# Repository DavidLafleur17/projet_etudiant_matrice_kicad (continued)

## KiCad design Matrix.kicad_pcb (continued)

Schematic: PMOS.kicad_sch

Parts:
Q2, Q3, Q4, Q5, Q6, Q7, Q8, Q9, Q10, Q11, Q12, Q13, Q14, Q15, Q16, Q17: PMOS; GSF3407; DigiKey PN 4786-GSFC3401CT-ND

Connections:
+5V: Q2.3 (S), Q3.3 (S), Q4.3 (S), Q5.3 (S), Q6.3 (S), Q7.3 (S), Q8.3 (S), Q9.3 (S), Q10.3 (S), Q11.3 (S), Q12.3 (S), Q13.3 (S), Q14.3 (S), Q15.3 (S), Q16.3 (S), Q17.3 (S); also elsewhere on the board
/Decoder/PMOS/DEC0: Q2.2 (G); also elsewhere on the board
/Decoder/PMOS/DEC1: Q3.2 (G); also elsewhere on the board
/Decoder/PMOS/DEC2: Q4.2 (G); also elsewhere on the board
/Decoder/PMOS/DEC3: Q5.2 (G); also elsewhere on the board
/Decoder/PMOS/DEC4: Q6.2 (G); also elsewhere on the board
/Decoder/PMOS/DEC5: Q7.2 (G); also elsewhere on the board
/Decoder/PMOS/DEC6: Q8.2 (G); also elsewhere on the board
/Decoder/PMOS/DEC7: Q9.2 (G); also elsewhere on the board
/Decoder/PMOS/DEC8: Q10.2 (G); also elsewhere on the board
/Decoder/PMOS/DEC9: Q11.2 (G); also elsewhere on the board
/Decoder/PMOS/DEC10: Q12.2 (G); also elsewhere on the board
/Decoder/PMOS/DEC11: Q13.2 (G); also elsewhere on the board
/Decoder/PMOS/DEC12: Q14.2 (G); also elsewhere on the board
/Decoder/PMOS/DEC13: Q15.2 (G); also elsewhere on the board
/Decoder/PMOS/DEC14: Q16.2 (G); also elsewhere on the board
/Decoder/PMOS/DEC15: Q17.2 (G); also elsewhere on the board
/Decoder/Row0: Q2.1 (D); also elsewhere on the board
/Decoder/Row1: Q3.1 (D); also elsewhere on the board
/Decoder/Row2: Q4.1 (D); also elsewhere on the board
/Decoder/Row3: Q5.1 (D); also elsewhere on the board
/Decoder/Row4: Q6.1 (D); also elsewhere on the board
/Decoder/Row5: Q7.1 (D); also elsewhere on the board
/Decoder/Row6: Q8.1 (D); also elsewhere on the board
/Decoder/Row7: Q9.1 (D); also elsewhere on the board
/Decoder/Row8: Q10.1 (D); also elsewhere on the board
/Decoder/Row9: Q11.1 (D); also elsewhere on the board
/Decoder/Row10: Q12.1 (D); also elsewhere on the board
/Decoder/Row11: Q13.1 (D); also elsewhere on the board
/Decoder/Row12: Q14.1 (D); also elsewhere on the board
/Decoder/Row13: Q15.1 (D); also elsewhere on the board
/Decoder/Row14: Q16.1 (D); also elsewhere on the board
/Decoder/Row15: Q17.1 (D); also elsewhere on the board

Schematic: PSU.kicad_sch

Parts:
C17, C18: 100nF; C_0805_2012Metric_Pad1.18x1.45mm_HandSolder; DigiKey PN 399-C0805F104K1RACAUTOCT-ND
C28: 47uF; CP_Elec_6.3x5.9; DigiKey PN EMZJ350ARA470MF61G
C29: 22nF; C_0805_2012Metric_Pad1.18x1.45mm_HandSolder; DigiKey PN 399-C0805C223K5RACTUCT-ND
D514: SMAJ5.0A; P6SMAJ5.0; DigiKey PN 31-P6SMAJ5.0ADF-13CT-ND
F1: 1.75A; Fuse_1206_3216Metric_Pad1.42x1.75mm_HandSolder; DigiKey PN 13-SMD1206B175TFCT-ND
J3: PSU HDR (mâle); PinHeader_1x03_P2.54mm_Horizontal; DigiKey PN S9403-ND
J5: PSU HDR (femelle); DigiKey PN S9434-ND
J9: Barrel_Jack_Switch; DigiKey PN CP-038A-ND
Q1: NMOS; GSF3407; DigiKey PN 4786-GSF3404BCT-ND
R32: 100kΩ; R_0805_2012Metric_Pad1.20x1.40mm_HandSolder; DigiKey PN 2019-RK73H2ATTD1003FCT-ND
U12: LM74700Q; TSOT-23-6_HandSoldering; DigiKey PN 296-LM74700QDBVRQ1CT-ND

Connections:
/Alimentation/PSU/PSU_V+: C18.1, C28.1, Q1.1 (D), U12.4 (CATHODE); also elsewhere on the board
GND: C18.2, C28.2, C29.2, D514.2 (A2), J3.2, J3.3, U12.2 (GND); also elsewhere on the board
unnamed: D514.1 (A1), F1.1, J3.1
unnamed: Q1.2 (G), U12.5 (GATE)
unnamed: C17.1, C29.1, F1.2, Q1.3 (S), R32.2, U12.6 (ANODE)
unnamed: R32.1, U12.3 (EN)
unnamed: C17.2, U12.1 (VCP)

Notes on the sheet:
Not on board

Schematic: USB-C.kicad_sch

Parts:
C1, C2: 100nF; C_0805_2012Metric_Pad1.18x1.45mm_HandSolder; DigiKey PN 399-C0805F104K1RACAUTOCT-ND
D513: SMAJ5.0A; P6SMAJ5.0; DigiKey PN 31-P6SMAJ5.0ADF-13CT-ND
D515, D516: ESD5V; D_0603_1608Metric_Pad1.05x0.95mm_HandSolder; DigiKey PN 31-D5V0S1U2LP1610-7CT-ND
J7: USB_C_Receptacle_USB2.0_16P; USB_C_Receptacle_GCT_USB4105-xx-A_16P_TopMnt_Horizontal; DigiKey PN 2223-UJ20-C-H-G-SMT-2A-P16-TRCT-ND
R1: 1MΩ; R_0805_2012Metric_Pad1.20x1.40mm_HandSolder; DigiKey PN 2019-RK73H2ATTD1004FCT-ND
R2, R3: 5.1kΩ; R_0805_2012Metric_Pad1.20x1.40mm_HandSolder; DigiKey PN 2019-RK73H2ATTD5101FCT-ND
R35: 33kΩ; R_0805_2012Metric_Pad1.20x1.40mm_HandSolder; DigiKey PN 2019-RK73H2ATTD3302FCT-ND
R36: 47kΩ; R_0805_2012Metric_Pad1.20x1.40mm_HandSolder; DigiKey PN 2019-RK73H2ATTD4702FCT-ND
R37: 1kΩ; R_0805_2012Metric_Pad1.20x1.40mm_HandSolder; DigiKey PN 2019-RK73H2ATTD1001FCT-ND

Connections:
/Alimentation/USB_D+: D515.2 (A2), J7.A6 (D+), J7.B6 (D+); also elsewhere on the board
/Alimentation/USB_D-: D516.2 (A2), J7.A7 (D-), J7.B7 (D-); also elsewhere on the board
/Alimentation/VBUS_SENSE: R37.1; also elsewhere on the board
GND: C1.2, C2.2, D513.2 (A2), D515.1 (A1), D516.1 (A1), J7.A1 (GND), J7.A12 (GND), J7.B1 (GND), J7.B12 (GND), R1.1, R2.1, R3.1, R36.2; also elsewhere on the board
unnamed: C2.1, R35.2, R36.1, R37.2
unnamed: D513.1 (A1), J7.A4 (VBUS), J7.A9 (VBUS), J7.B4 (VBUS), J7.B9 (VBUS), R35.1
unnamed: J7.A5 (CC1), R2.2
unnamed: J7.B5 (CC2), R3.2
unnamed: C1.1, J7.S1 (SHIELD), R1.2

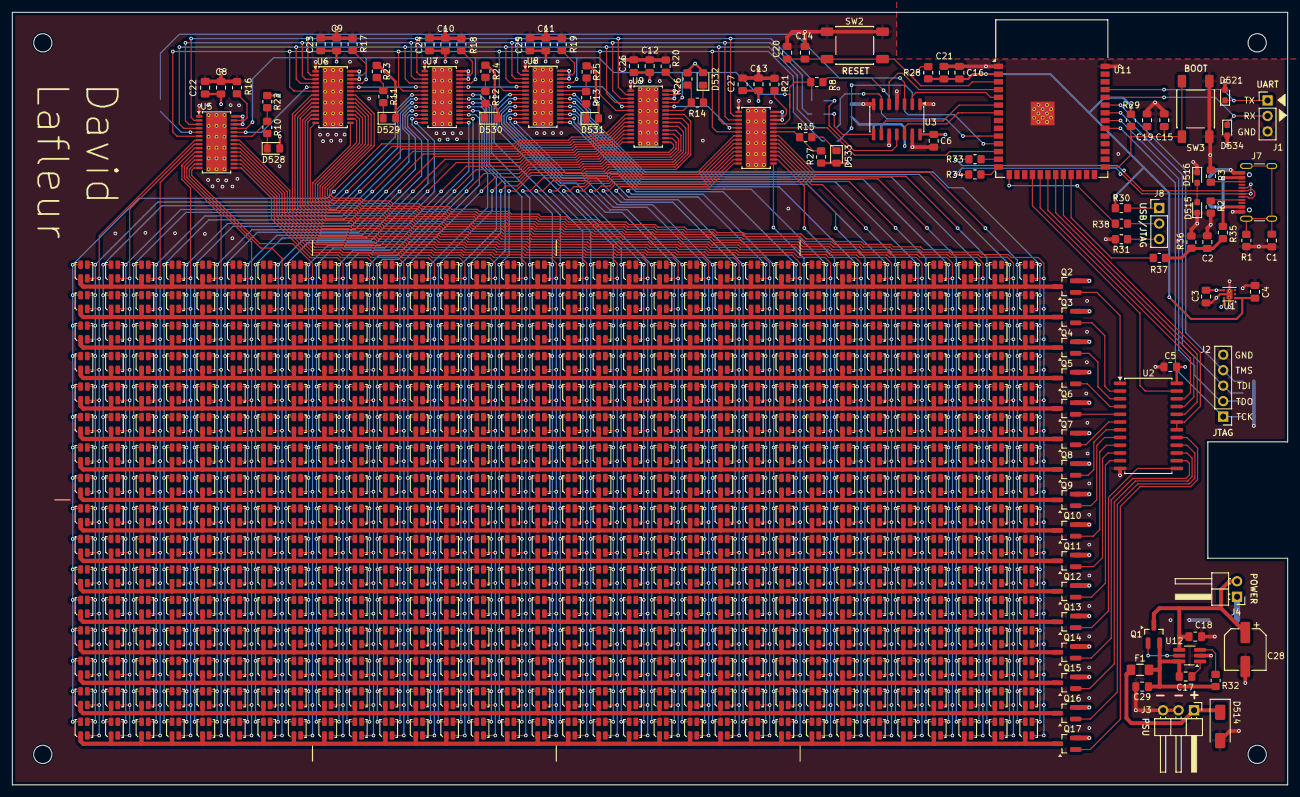
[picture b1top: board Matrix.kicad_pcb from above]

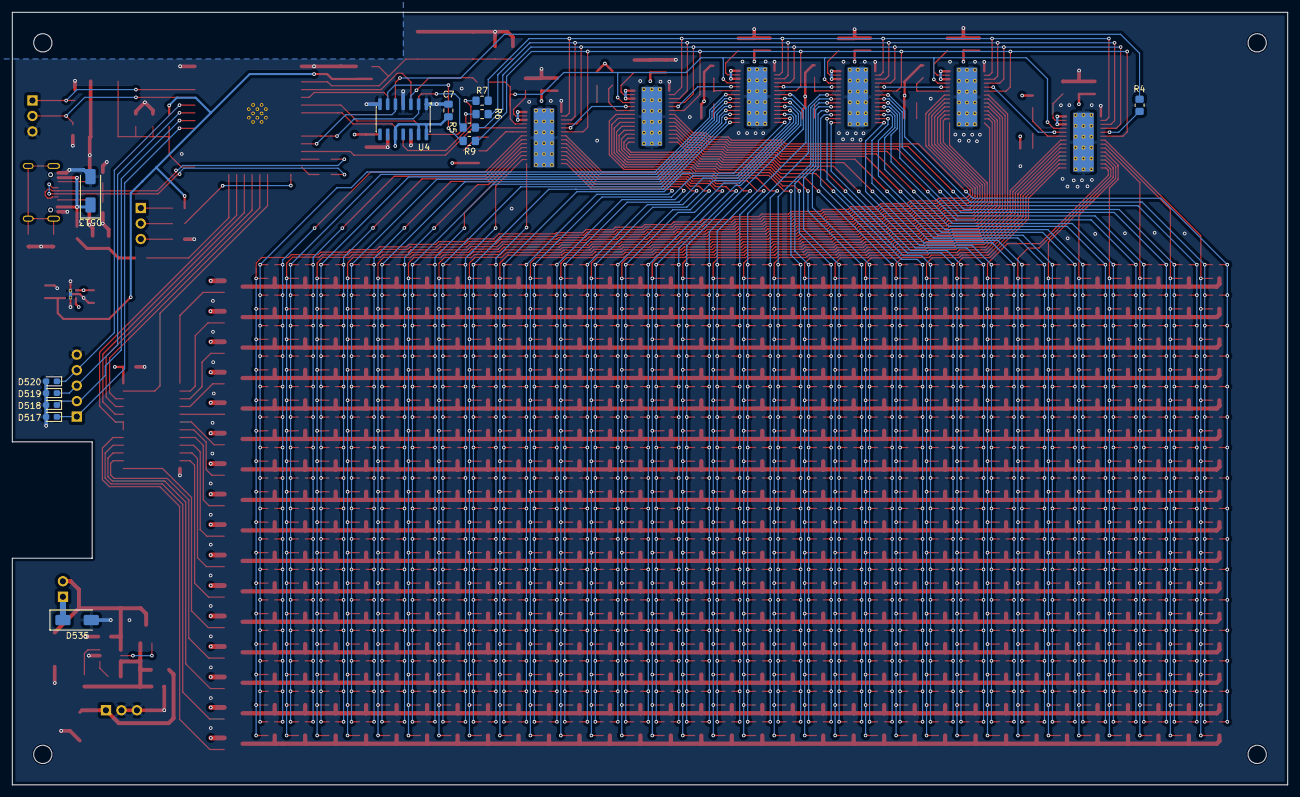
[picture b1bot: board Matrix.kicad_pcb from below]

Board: 4 copper layers, 209.2 x 126.8 mm, 638 parts (13 on the bottom side), 206 nets.

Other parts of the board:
U7, U8, U9, U10: TLC5940PWP; HTSSOP-28-1EP_4.4x9.7mm_P0.65mm_EP3.4x9.5mm_Mask2.4x6.17mm_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

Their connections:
+5V: U7.26 (DCPRG), U7.28 (VCC), U8.26 (DCPRG), U8.28 (VCC), U9.26 (DCPRG), U9.28 (VCC), U10.26 (DCPRG), U10.28 (VCC); also elsewhere on the board
/Blue0: U9.7 (OUT0); also elsewhere on the board
/Blue1: U9.8 (OUT1); also elsewhere on the board
/Blue2: U9.9 (OUT2); also elsewhere on the board
/Blue3: U9.10 (OUT3); also elsewhere on the board
/Blue4: U9.11 (OUT4); also elsewhere on the board
/Blue5: U9.12 (OUT5); also elsewhere on the board
/Blue6: U9.13 (OUT6); also elsewhere on the board
/Blue7: U9.14 (OUT7); also elsewhere on the board
/Blue8: U9.15 (OUT8); also elsewhere on the board
/Blue9: U9.16 (OUT9); also elsewhere on the board
/Blue10: U9.17 (OUT10); also elsewhere on the board
/Blue11: U9.18 (OUT11); also elsewhere on the board
/Blue12: U9.19 (OUT12); also elsewhere on the board
/Blue13: U9.20 (OUT13); also elsewhere on the board
/Blue14: U9.21 (OUT14); also elsewhere on the board
/Blue15: U9.22 (OUT15); also elsewhere on the board
/Blue16: U10.7 (OUT0); also elsewhere on the board
/Blue17: U10.8 (OUT1); also elsewhere on the board
/Blue18: U10.9 (OUT2); also elsewhere on the board
/Blue19: U10.10 (OUT3); also elsewhere on the board
/Blue20: U10.11 (OUT4); also elsewhere on the board
/Blue21: U10.12 (OUT5); also elsewhere on the board
/Blue22: U10.13 (OUT6); also elsewhere on the board
/Blue23: U10.14 (OUT7); also elsewhere on the board
/Blue24: U10.15 (OUT8); also elsewhere on the board
/Blue25: U10.16 (OUT9); also elsewhere on the board
/Blue26: U10.17 (OUT10); also elsewhere on the board
/Blue27: U10.18 (OUT11); also elsewhere on the board
/Blue28: U10.19 (OUT12); also elsewhere on the board
/Blue29: U10.20 (OUT13); also elsewhere on the board
/Blue30: U10.21 (OUT14); also elsewhere on the board
/Blue31: U10.22 (OUT15); also elsewhere on the board
/Green0: U7.7 (OUT0); also elsewhere on the board
/Green1: U7.8 (OUT1); also elsewhere on the board
/Green2: U7.9 (OUT2); also elsewhere on the board
/Green3: U7.10 (OUT3); also elsewhere on the board
/Green4: U7.11 (OUT4); also elsewhere on the board
/Green5: U7.12 (OUT5); also elsewhere on the board
/Green6: U7.13 (OUT6); also elsewhere on the board
/Green7: U7.14 (OUT7); also elsewhere on the board
/Green8: U7.15 (OUT8); also elsewhere on the board
/Green9: U7.16 (OUT9); also elsewhere on the board
/Green10: U7.17 (OUT10); also elsewhere on the board
/Green11: U7.18 (OUT11); also elsewhere on the board
/Green12: U7.19 (OUT12); also elsewhere on the board
/Green13: U7.20 (OUT13); also elsewhere on the board
/Green14: U7.21 (OUT14); also elsewhere on the board
/Green15: U7.22 (OUT15); also elsewhere on the board
/Green16: U8.7 (OUT0); also elsewhere on the board
/Green17: U8.8 (OUT1); also elsewhere on the board
/Green18: U8.9 (OUT2); also elsewhere on the board
/Green19: U8.10 (OUT3); also elsewhere on the board
/Green20: U8.11 (OUT4); also elsewhere on the board
/Green21: U8.12 (OUT5); also elsewhere on the board
/Green22: U8.13 (OUT6); also elsewhere on the board
/Green23: U8.14 (OUT7); also elsewhere on the board
/Green24: U8.15 (OUT8); also elsewhere on the board
/Green25: U8.16 (OUT9); also elsewhere on the board
/Green26: U8.17 (OUT10); also elsewhere on the board
/Green27: U8.18 (OUT11); also elsewhere on the board
/Green28: U8.19 (OUT12); also elsewhere on the board
/Green29: U8.20 (OUT13); also elsewhere on the board
/Green30: U8.21 (OUT14); also elsewhere on the board
/Green31: U8.22 (OUT15); also elsewhere on the board
/TLC_BLANK: U7.2 (BLANK), U8.2 (BLANK), U9.2 (BLANK), U10.2 (BLANK); also elsewhere on the board
/TLC_BLUE/TLC SIN: U8.24 (SOUT), U9.5 (SIN)
/TLC_GREEN/TLC SIN: U7.5 (SIN); also elsewhere on the board
/TLC_GSCLK: U7.25 (GSCLK), U8.25 (GSCLK), U9.25 (GSCLK), U10.25 (GSCLK); also elsewhere on the board
/TLC_SCLK: U7.4 (SCLK), U8.4 (SCLK), U9.4 (SCLK), U10.4 (SCLK); also elsewhere on the board
/TLC_VPRG: U7.6 (VPRG), U8.6 (VPRG), U9.6 (VPRG), U10.6 (VPRG); also elsewhere on the board
/TLC_XLAT: U7.3 (XLAT), U8.3 (XLAT), U9.3 (XLAT), U10.3 (XLAT); also elsewhere on the board
GND: U7.1 (GND), U7.29 (PAD), U8.1 (GND), U8.29 (PAD), U9.1 (GND), U9.29 (PAD), U10.1 (GND), U10.29 (PAD); also elsewhere on the board
unnamed 188: U7.27 (IREF); also elsewhere on the board
unnamed: U7.24 (SOUT), U8.5 (SIN)
unnamed 190: U7.23 (XERR); also elsewhere on the board
unnamed 191: U8.27 (IREF); also elsewhere on the board
unnamed 192: U8.23 (XERR); also elsewhere on the board
unnamed 193: U9.27 (IREF); also elsewhere on the board
unnamed 194: U9.23 (XERR); also elsewhere on the board
unnamed 195: U10.27 (IREF); also elsewhere on the board
unnamed: U9.24 (SOUT), U10.5 (SIN)
unnamed 197: U10.23 (XERR); also elsewhere on the board
TLC_SOUT: U10.24 (SOUT); also elsewhere on the board

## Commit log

2026-06-01 Schemas kicad pour matrice lors du 31 mai 2026
